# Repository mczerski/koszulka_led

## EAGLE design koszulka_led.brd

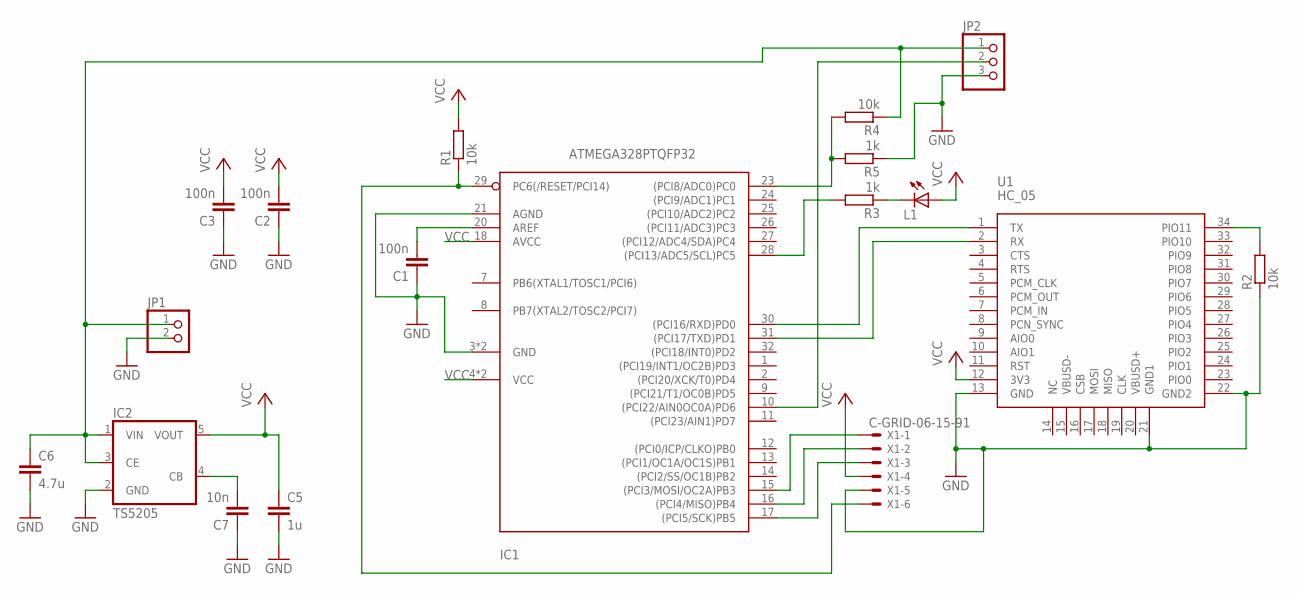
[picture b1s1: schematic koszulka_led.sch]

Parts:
C1, C2, C3: 100n; C0402
C5: 1u; C0805
C6: 4.7u; C0805
C7: 10n; C0402
IC1: ATMEGA328PTQFP32; TQFP32-08
IC2: TS5205; SOT25
JP1: PINHD-1X2; 1X02
JP2: PINHD-1X3; 1X03
L1: LEDCHIP-LED0603; CHIP-LED0603
R1, R2, R4: 10k; R0603
R3, R5: 1k; R0603
U1: HC_05; BLUETOOTH_SMD
X1: C-GRID-06-15-91; 15-91-06

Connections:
GND: C1.1, C2.1, C3.1, C5.2, C6.2, C7.1, IC1.3 (GND), IC1.5 (GND), IC1.21 (AGND), IC2.2 (GND), JP1.2, JP2.3, R2.1, R5.1, U1.13 (GND), U1.21 (GND1), U1.22 (GND2), X1.5
unnamed: IC1.29 (PC6(/RESET/PCI14)), R1.1, X1.6
unnamed: C1.2, IC1.20 (AREF)
unnamed: IC1.30 ((PCI16/RXD)PD0), U1.1 (TX)
unnamed: IC1.31 ((PCI17/TXD)PD1), U1.2 (RX)
unnamed: IC1.17 ((PCI5/SCK)PB5), X1.3
unnamed: IC1.16 ((PCI4/MISO)PB4), X1.2
unnamed: R2.2, U1.34 (PIO11)
unnamed: IC1.15 ((PCI3/MOSI/OC2A)PB3), X1.1
unnamed: C6.1, IC2.1 (VIN), IC2.3 (CE), JP1.1, JP2.1, R4.1
unnamed: IC1.10 ((PCI22/AIN0OC0A)PD6), JP2.2
unnamed: C7.2, IC2.4 (CB)
unnamed: IC1.28 ((PCI13/ADC5/SCL)PC5), R3.2
unnamed: L1.C, R3.1
unnamed: IC1.23 ((PCI8/ADC0)PC0), R4.2, R5.2
VCC: C2.2, C3.2, C5.1, IC1.4 (VCC), IC1.6 (VCC), IC1.18 (AVCC), IC2.5 (VOUT), L1.A, R1.2, U1.12 (3V3), X1.4

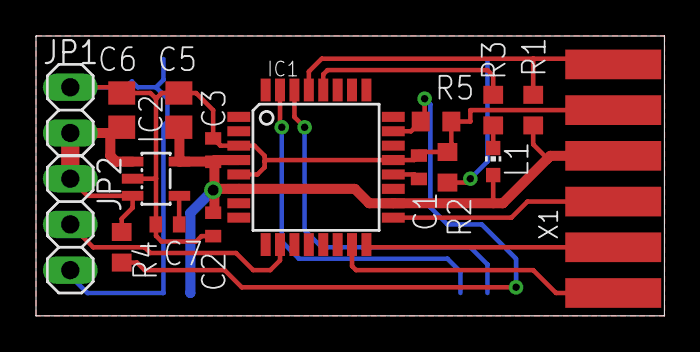
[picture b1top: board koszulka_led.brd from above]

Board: 2 copper layers, 34.9 x 15.5 mm, 18 parts (1 on the bottom side), 16 nets.

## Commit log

2015-05-01 pierwszy commit - wersja 0.1
